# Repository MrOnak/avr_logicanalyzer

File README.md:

avr_logicanalyzer
=================

A barebones 8 channel logic analyzer

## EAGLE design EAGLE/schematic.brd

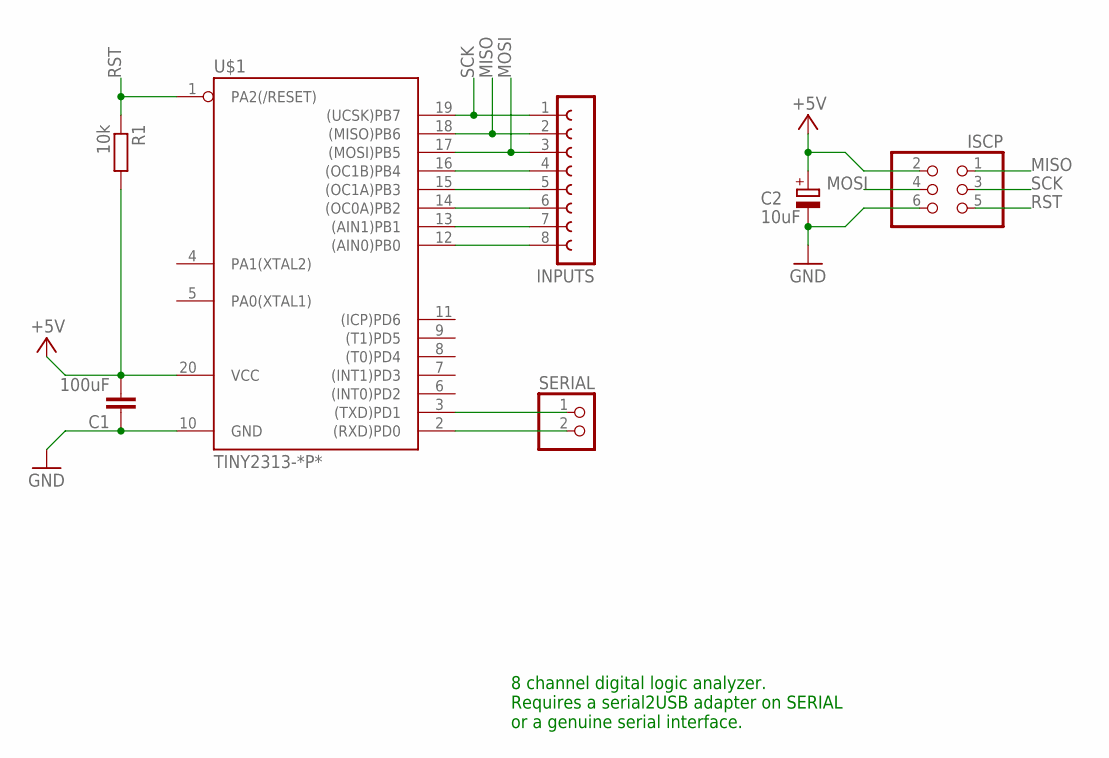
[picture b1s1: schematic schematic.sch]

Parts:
C1: 100uF; C025-024X044
C2: 10uF; E2,5-6
INPUTS: FE08W
ISCP: PINHD-2X3; 2X03
R1: 10k; 0204V
SERIAL: PINHD-1X2; 1X02
U$1: TINY2313-*P*; DIL20

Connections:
+5V: C1.2, C2.+, ISCP.2, R1.2, U$1.20 (VCC)
GND: C1.1, C2.-, ISCP.6, U$1.10 (GND)
MISO: INPUTS.2, ISCP.1, U$1.18 ((MISO)PB6)
MOSI: INPUTS.3, ISCP.4, U$1.17 ((MOSI)PB5)
unnamed: SERIAL.1, U$1.3 ((TXD)PD1)
unnamed: SERIAL.2, U$1.2 ((RXD)PD0)
unnamed: INPUTS.4, U$1.16 ((OC1B)PB4)
unnamed: INPUTS.5, U$1.15 ((OC1A)PB3)
unnamed: INPUTS.6, U$1.14 ((OC0A)PB2)
unnamed: INPUTS.7, U$1.13 ((AIN1)PB1)
unnamed: INPUTS.8, U$1.12 ((AIN0)PB0)
RST: ISCP.5, R1.1, U$1.1 (PA2(/RESET))
SCK: INPUTS.1, ISCP.3, U$1.19 ((UCSK)PB7)

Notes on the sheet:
8 channel digital logic analyzer. Requires a serial2USB adapter on SERIAL or a genuine serial interface.

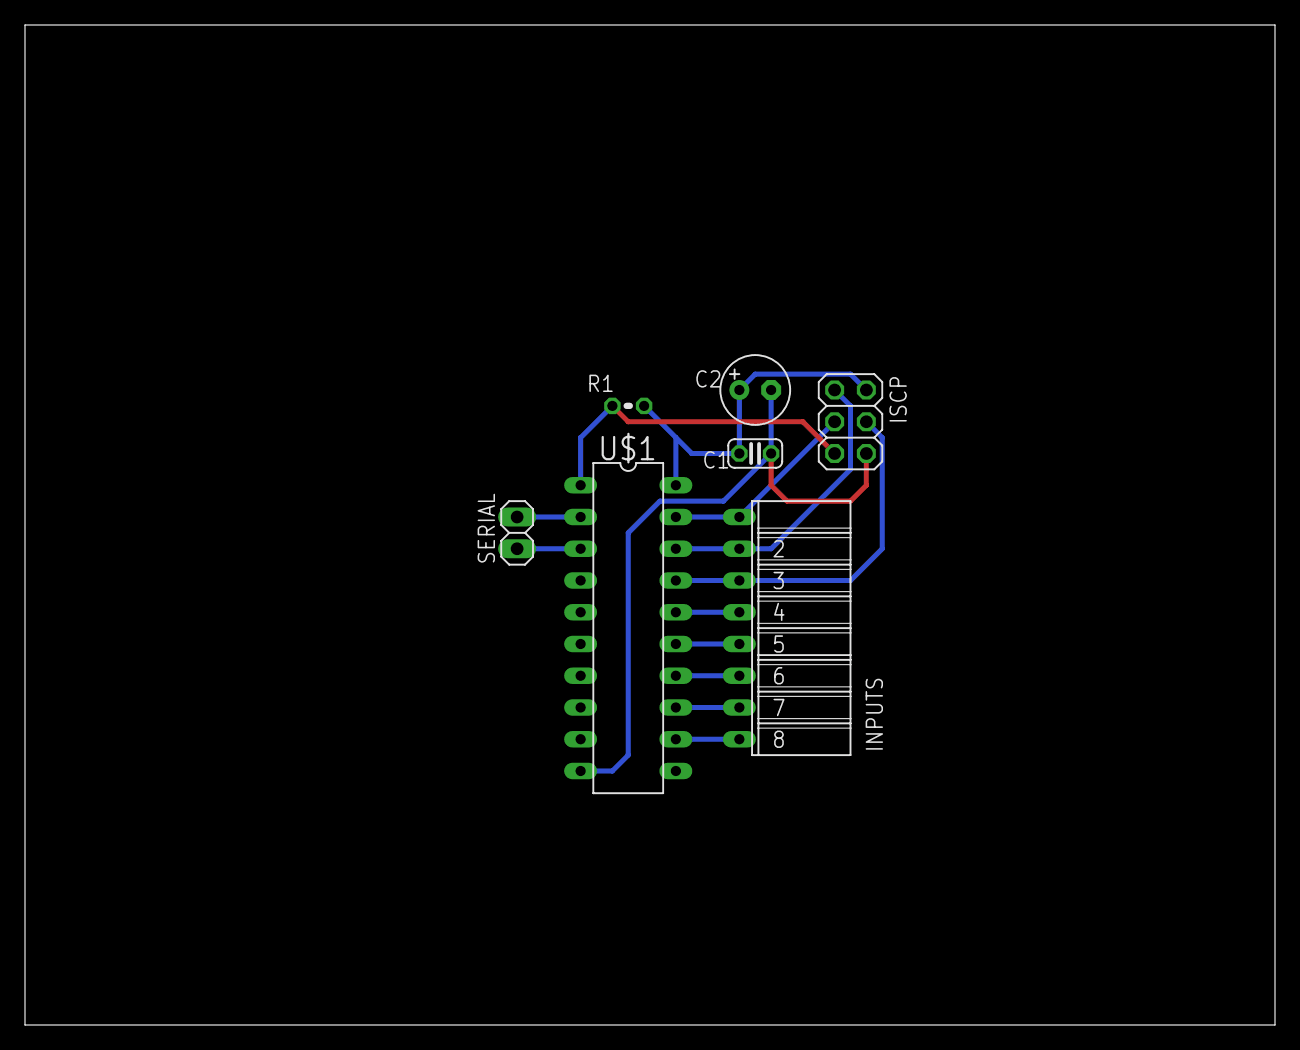
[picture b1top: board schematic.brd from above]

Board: 2 copper layers, 100.0 x 80.0 mm, 7 parts (0 on the bottom side), 13 nets.

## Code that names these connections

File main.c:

/**
 * Logic Analyzer based around an ATTiny2313
 *
 * Constantly pumps out the values of the PINB register via Serial
 * The Serial connection runs at 38400 baud.
 *
 * Higher Baudrates are probably possible when the MUC is clocked higher
 * than the 8MHz internal clock but I have had inconsistency issues
 * when I tried with 8MHz.
 */
#include <stdlib.h>
#include <avr/io.h>
#include <avr/interrupt.h>
#include <avr/pgmspace.h>
#include <util/delay.h>

#include "main.h"
#include "uart/uart.h"

/**
 * Will constantly pump out the value of the PINB register
 *
 */
int main() {
  init();

  while (1) {
    commandParser();
    
    if (running == 1) {
      if (triggered == 0 && noTrigger == 0) {
        checkTriggers();
        lastData = PINB;
      } else {
        writeToBuffer();
      }
    }
  }

  return 0;
}

/**
 * Initializes the PB register as pullup-inputs and starts UART
 */
void init() {
    uart_init( UART_BAUD_SELECT(UART_BAUD_RATE,F_CPU) ); 
    sei();
    
    // set all PINB pins as inputs with pullups
    DDRD  &= ~(1 << PB0) | ~(1 << PB1) | ~(1 << PB2) | ~(1 << PB3) | ~(1 << PB4) | ~(1 << PB5) | ~(1 << PB6) | ~(1 << PB7);
    PORTB |=  (1 << PB0) |  (1 << PB1) |  (1 << PB2) |  (1 << PB3) |  (1 << PB4) |  (1 << PB5) |  (1 << PB6) |  (1 << PB7);
    
    // set all flags
    running = 0;
    triggers[0] = 0x00;
    triggers[1] = 0x00;
    noTrigger = 1;
    triggered = 0;
    lastData = 0x00;
    
    //uart_puts_P("8 channel Logic Analyzer ready");
    
}

/**
 * reads commands from UART and calls the appropriate subroutine
 */
void commandParser() {
  if (uart_available() > 0) {
    uint16_t c = uart_getc();
    uint16_t c2;
    
    if ( c & UART_NO_DATA ) {
      // no data available from UART 
    } else {
      // new data available from UART - check for Frame or Overrun error
      if ( c & UART_FRAME_ERROR ) {
        // Framing Error detected, i.e no stop bit detected
        uart_puts_P("UART Frame Error: ");
      }
      
      if ( c & UART_OVERRUN_ERROR ) {
        // Overrun, a character already present in the UART UDR register was not read by the interrupt handler 
        // before the next character arrived, one or more received characters have been dropped
        uart_puts_P("UART Overrun Error: ");
      }
      if ( c & UART_BUFFER_OVERFLOW ) {
        //We are not reading the receive buffer fast enough, one or more received character have been dropped 
        uart_puts_P("Buffer overflow error: ");
      }
      
      switch (c) {
        case CMD_SEND_MAX_BUFFER_SIZE:  // 'm'
          cmdSendMaxBufferSize();
          break;
        case CMD_SEND_BUFFER_SIZE:      // 'b'
          cmdSendBufferSize();
          break;
        case CMD_SET_BUFFER_SIZE:       // 'M'
          while (uart_available() == 0) {}
          c = uart_getc();
          if ((c >> 8) == 0) {
            cmdSetBufferSize(c);
          } else {
            sendNack();
          }
          break;
        case CMD_SET_TRIGGER:           // 'T'
          while (uart_available() < 2) {}
          c = uart_getc();
          c2 = uart_getc();
          if ((c >> 8) == 0 && (c2 >> 8) == 0) {
            cmdSetTrigger(c, c2);
          } else {
            sendNack();
          }
          break;
        case CMD_GET_TRIGGER:           // 't'
          cmdGetTrigger();
          break;
        case CMD_NO_TRIGGER:            // 'N'
          cmdNoTrigger();
          break;
        case CMD_START:                 // 'S'
          cmdStart();
          break;
        case CMD_STOP:                  // 's'
          cmdStop();
          break;
        case CMD_SEND_BUFFER:           // 'B'
          cmdSendBuffer();
          break;
        default:
          sendErr(ERR_INVALID_COMMAND);
      }
    }    
  }
}

/**
 * sends the maximum allowed buffer size to the client
 */
void cmdSendMaxBufferSize() {
  sendAck();
  uart_putc(MAX_BUFFER_SIZE);
}

/**
 * sends the current buffer size to the client
 */
void cmdSendBufferSize() {
  sendAck();
  uart_putc(bufferSize);
}

/**
 * sets the ring buffer to the given size
 */
void cmdSetBufferSize(uint8_t size) {
  if (size <= MAX_BUFFER_SIZE) {
    bufferSize = size;
    sendAck();
  } else {
    sendErr(ERR_BUFFER_TOO_LARGE);
  }    
}

/**
 * configures the input triggers and sets
 * the noTrigger flag to 0.
 */
void cmdSetTrigger(uint8_t rising, uint8_t falling) {
  noTrigger = 0;
  triggers[0] = rising;
  triggers[1] = falling;
  sendAck();
}

 /**
  * erases input triggers and sets the noTrigger flag
  *
  * this will cause data gathering to immediately start
  * after cmdStart() is being issued.
  */
 void cmdNoTrigger() {
   noTrigger = 1;
   triggers[0] = 0x00;
   triggers[1] = 0x00;
   sendAck();
}

/**
 * sends the rising and falling trigger bitmasks (in that order)
 */
void cmdGetTrigger() {
  uart_putc(triggers[0]);
  uart_putc(triggers[1]);  
}
 
 
/**
 * starts input gathering. also resets the buffer position
 * to zero, effectively erasing the buffer as it's being read later
 */
void cmdStart() {
  uint8_t i;
  
  if (running == 0) {
    bufferPos = 0;
    running = 1;
    triggered = 0;
    lastData = PINB;
    
    for (i = 0; i < MAX_BUFFER_SIZE; i++) {
      buffer[i] = 0x00;
    }
    
    sendAck();
  } else {
    sendErr(ERR_RUNNING);
  }
}

/**
 * stops the data gathering
 *
 * this is useful in case the triggers don't get triggered.
 *
 * will set running to 0
 */
void cmdStop() {
  running = 0;
  sendAck();
}

/** 
 * sends the recorded data buffer to the client
 */
void cmdSendBuffer() {
  uint8_t i;
  
  if (running == 0) {
    for (i = 0; i < bufferSize; i++) {
      uart_putc(buffer[i]);
    }
  } else {
    sendErr(ERR_RUNNING);
  }
}

/**
 * sends an acknowledgement byte
 */
void sendAck() {
  uart_putc(ACK);
}

/**
 * sends a generic not-acknowledged byte
 */
void sendNack() {
  uart_putc(NACK);
}

/**
 * sends an error
 */
void sendErr(uint16_t err) {
  uart_putc(err >> 8);
  uart_putc(err);
}

/**
 * checks the data register against trigger conditions
 * and resets the triggered flag if they match
 */ 
void checkTriggers() {
  // @todo implement checkTriggers()
}

/**
 * writes the current state of PINB into the ringbuffer
 * and advances the position.
 *
 * If the position reaches the bufferSize then reading is
 * terminated.
 *
 * once reading is finished an ACK will be sent
 */
void writeToBuffer() {
  buffer[bufferPos] = PINB;
  bufferPos++;
  
  // stop reading if buffer size is reached
  if (bufferPos == bufferSize) {
    running   = 0;
    triggered = 0;
    uart_putc(READY);
  }
}

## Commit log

2015-01-05 initial version
2015-01-05 fixed Readme
2015-01-06 changed 'protocol' to send one start character, then the register value, then CR/NL to make reading on Java side easier
2015-01-06 added licensing info to readme
2015-01-06 updated comments
2015-01-07 minimalistic & high speed transfer protocol to see how fast Java can read
2015-01-07 implemented a full-blown serial client that samples data only after being told so to reduce load on Java serial client.
